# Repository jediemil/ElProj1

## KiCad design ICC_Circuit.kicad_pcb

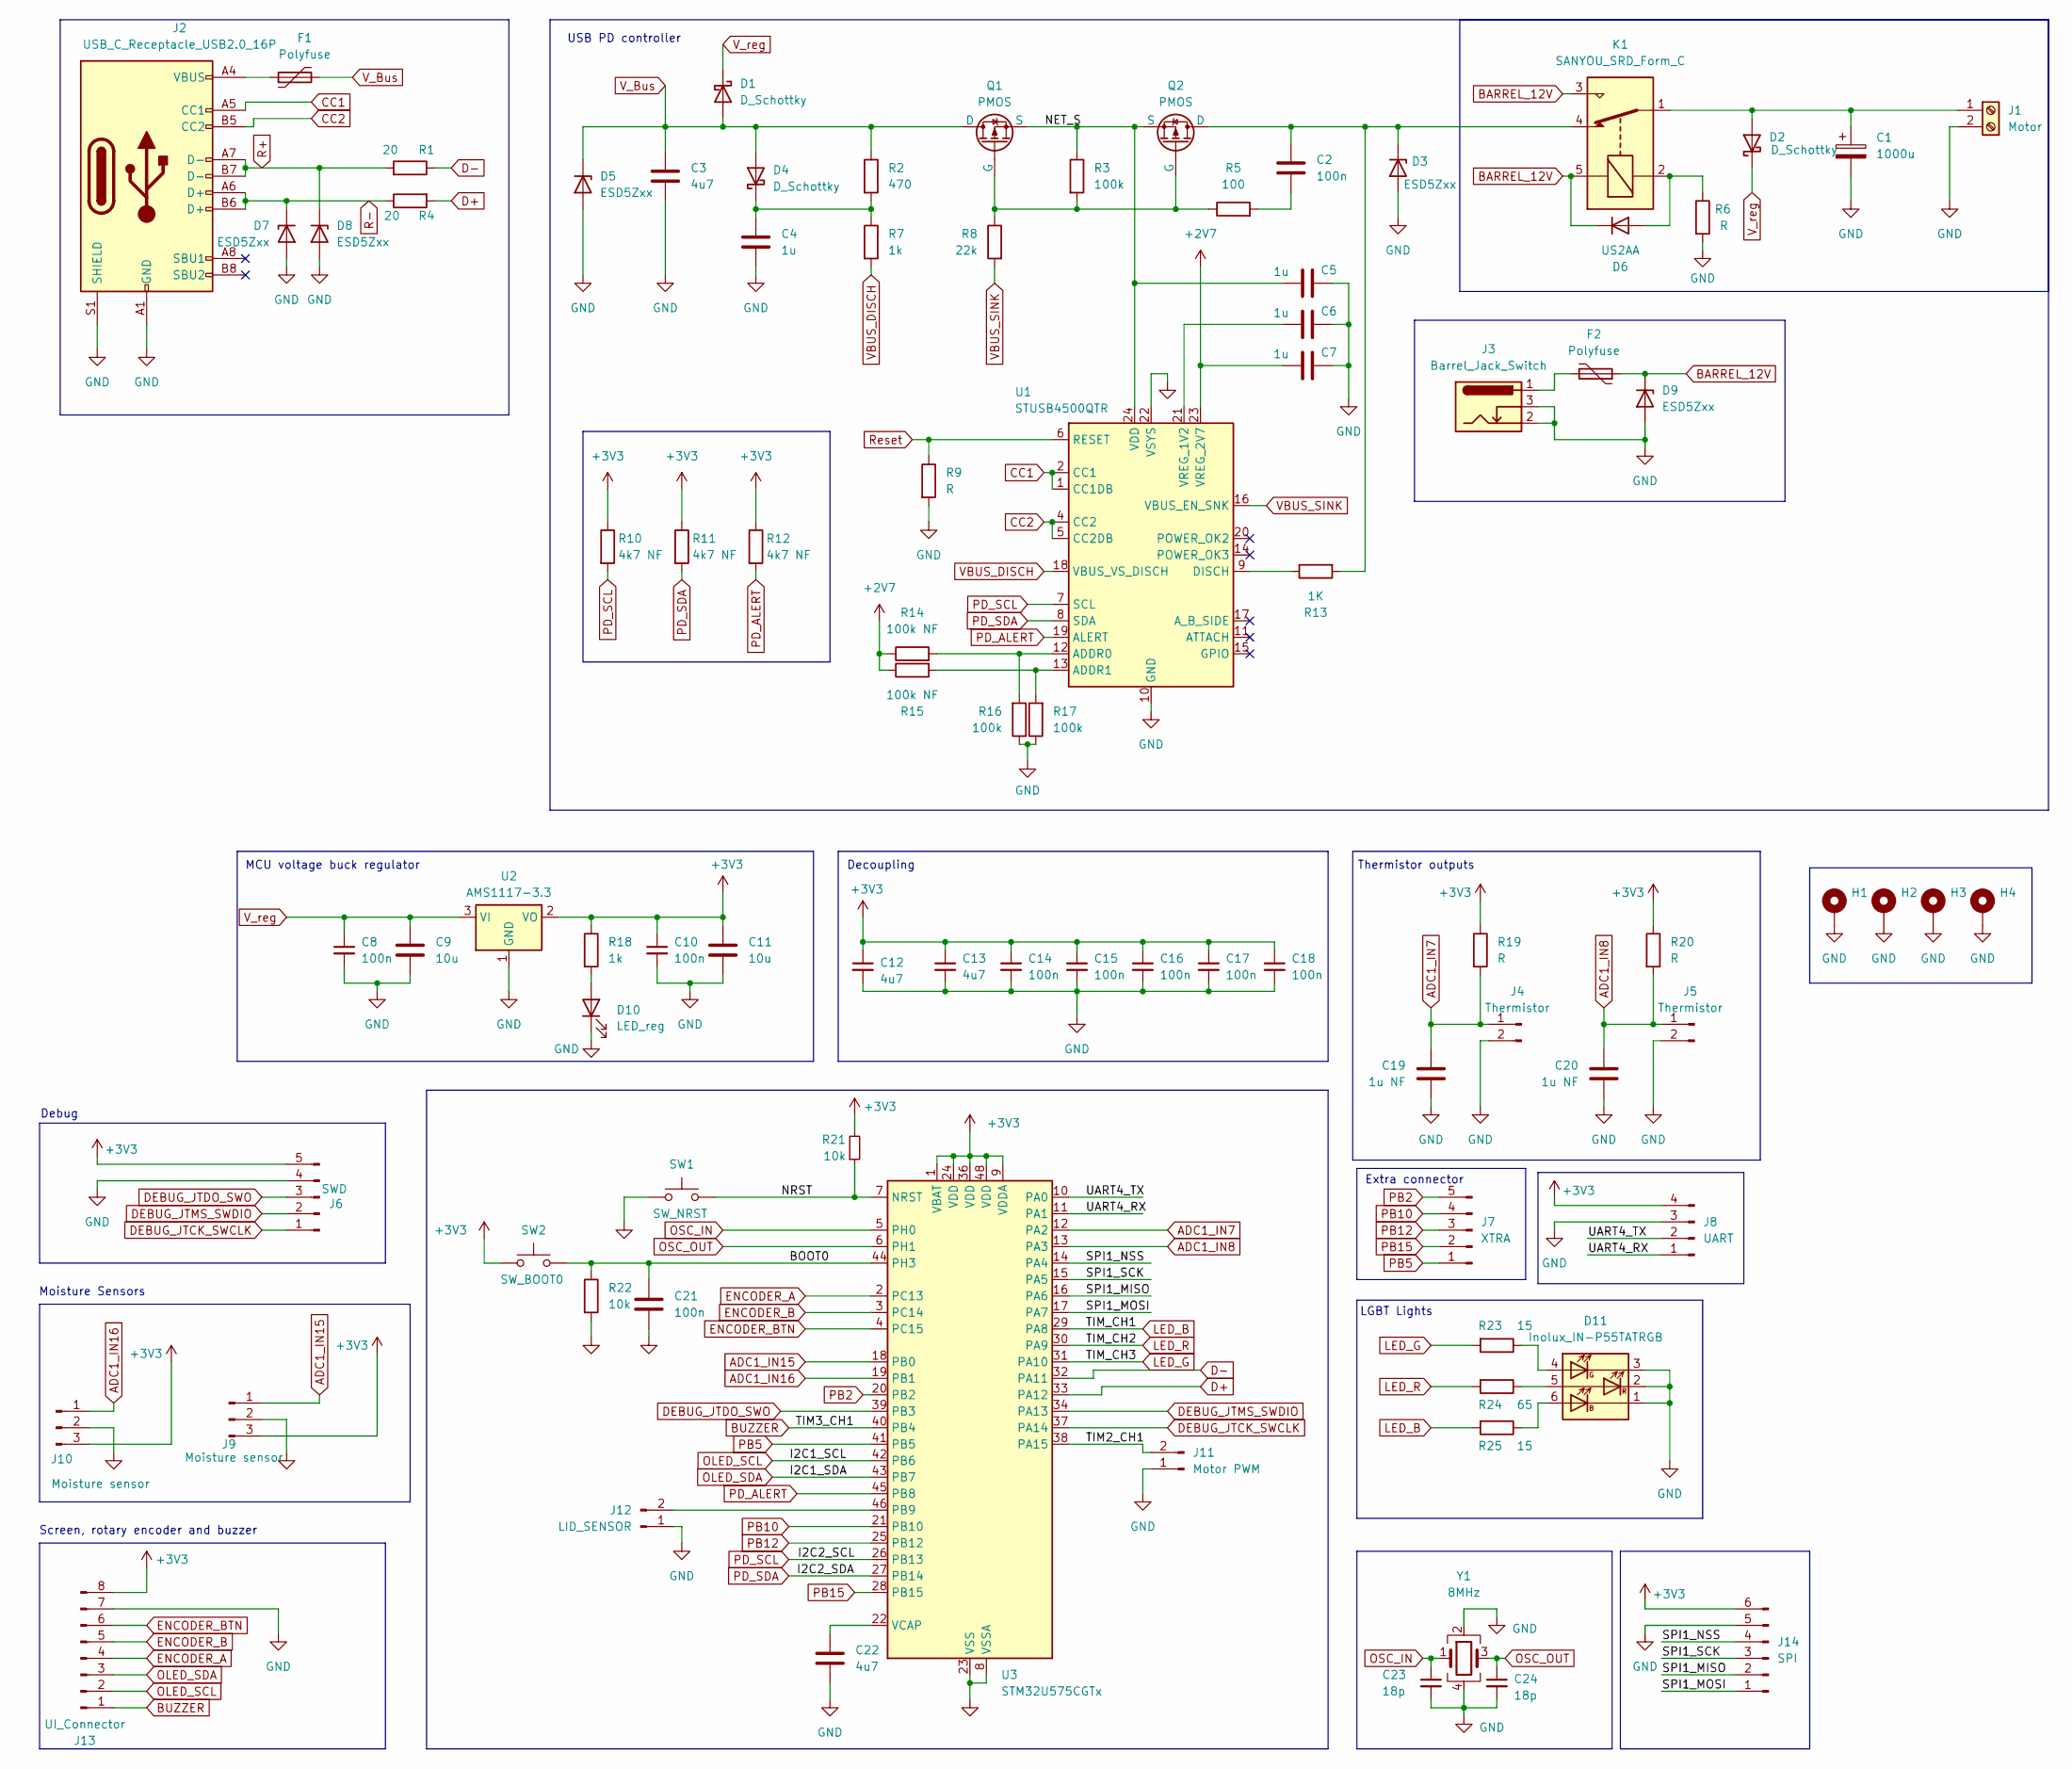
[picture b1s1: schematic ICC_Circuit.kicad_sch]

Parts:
C1: 1000u; CP_Radial_D10.0mm_P5.00mm
C2, C8, C10, C14, C15, C16, C17, C18, C21: 100n; C_0603_1608Metric
C3, C12, C13, C22: 4u7; C_0603_1608Metric
C4, C5, C6, C7: 1u; C_0603_1608Metric
C9, C11: 10u; C_0603_1608Metric
C19, C20: 1u NF; C_0603_1608Metric
C23, C24: 18p; C_0603_1608Metric
D1, D2, D4: D_Schottky; SOT-23_SpecialNC_Schottky
D3, D5, D7, D8, D9: ESD5Zxx; D_SMB
D6: US2AA; D_SMA
D10: LED_reg; LED_0603_1608Metric
D11: Inolux_IN-P55TATRGB; LED_Inolux_IN-P55TATRGB_PLCC6_5.0x5.5mm_P1.8mm
F1, F2: Polyfuse; 0ZRP0400FF custom Fuse
H1, H2, H3, H4: MountingHole_Pad; MountingHole_3.2mm_M3
J1: Motor; TerminalBlock_bornier-2_P5.08mm
J2: USB_C_Receptacle_USB2.0_16P; USB_C_Receptacle_GCT_USB4105-xx-A_16P_TopMnt_Horizontal
J3: Barrel_Jack_Switch; BarrelJack_GCT_DCJ200-10-A_Horizontal
J4, J5: Thermistor; JST_XH_S2B-XH-A-1_1x02_P2.50mm_Horizontal
J6: SWD; PinHeader_1x05_P2.54mm_Vertical
J7: XTRA; PinHeader_1x05_P2.54mm_Vertical
J8: UART; PinHeader_1x04_P2.54mm_Vertical
J9, J10: Moisture sensor; JST_XH_S3B-XH-A-1_1x03_P2.50mm_Horizontal
J11: Motor PWM; PinHeader_1x02_P2.54mm_Vertical
J12: LID_SENSOR; JST_XH_S2B-XH-A-1_1x02_P2.50mm_Horizontal
J13: UI_Connector; JST_XH_S8B-XH-A-1_1x08_P2.50mm_Horizontal
J14: SPI; PinHeader_1x06_P2.54mm_Vertical
K1: SANYOU_SRD_Form_C; Relay_SPDT_SANYOU_SRD_Series_Form_C
Q1, Q2: PMOS; Custom_PMOS_bajs_TSOP-6_1.65x3.05mm_P0.95mm
R1, R4: 20; R_0603_1608Metric
R2: 470; R_0603_1608Metric
R3, R16, R17: 100k; R_0603_1608Metric
R5: 100; R_0603_1608Metric
R6, R9, R19, R20: R; R_0603_1608Metric
R7, R18: 1k; R_0603_1608Metric
R8: 22k; R_0603_1608Metric
R10, R11, R12: 4k7 NF; R_0603_1608Metric
R13: 1K; R_0603_1608Metric
R14, R15: 100k NF; R_0603_1608Metric
R21, R22: 10k; R_0603_1608Metric
R23, R25: 15; R_0603_1608Metric
R24: 65; R_0603_1608Metric
SW1: SW_NRST; CharliesButton
SW2: SW_BOOT0; CharliesButton
U1: STUSB4500QTR; QFN-24-1EP_4x4mm_P0.5mm_EP2.7x2.7mm
U2: AMS1117-3.3; SOT-223-3_TabPin2
U3: STM32U575CGTx; LQFP-48_7x7mm_P0.5mm
Y1: 8MHz; Crystal_SMD_3225-4Pin_3.2x2.5mm_HandSoldering

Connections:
+2V7: C7.1, R14.1, R15.1, U1.23 (VREG_2V7)
+3V3: C10.1, C11.1, C12.1, C13.1, C14.1, C15.1, C16.1, C17.1, C18.1, J6.5, J8.4, J9.3, J10.3, J13.8, J14.6, R10.1, R11.1, R12.1, R18.1, R19.1, R20.1, R21.2, SW2.1, U2.2 (VO), U3.1 (VBAT), U3.9 (VDDA), U3.24 (VDD), U3.36 (VDD), U3.48 (VDD)
/BOOT0: C21.1, R22.1, SW2.2, U3.44 (PH3)
/NET_S: C5.1, Q1.3 (S), Q2.3 (S), R3.1, U1.24 (VDD)
/NRST: R21.1, SW1.2, U3.7 (NRST)
/SPI1_MISO: J14.2, U3.16 (PA6)
/SPI1_MOSI: J14.1, U3.17 (PA7)
/SPI1_NSS: J14.4, U3.14 (PA4)
/SPI1_SCK: J14.3, U3.15 (PA5)
/TIM2_CH1: J11.2, U3.38 (PA15)
/UART4_RX: J8.1, U3.11 (PA1)
/UART4_TX: J8.2, U3.10 (PA0)
ADC1_IN7: C19.1, J4.1, R19.2, U3.12 (PA2)
ADC1_IN8: C20.1, J5.1, R20.2, U3.13 (PA3)
ADC1_IN15: J9.1, U3.18 (PB0)
ADC1_IN16: J10.1, U3.19 (PB1)
BARREL_12V: D6.1 (K), D9.1 (K), F2.1, K1.3, K1.5
BUZZER: J13.1, U3.40 (PB4)
CC1: J2.A5 (CC1), U1.1 (CC1DB), U1.2 (CC1)
CC2: J2.B5 (CC2), U1.4 (CC2), U1.5 (CC2DB)
D+: R4.2, U3.33 (PA12)
D-: R1.1, U3.32 (PA11)
DEBUG_JTCK_SWCLK: J6.1, U3.37 (PA14)
DEBUG_JTDO_SWO: J6.3, U3.39 (PB3)
DEBUG_JTMS_SWDIO: J6.2, U3.34 (PA13)
ENCODER_A: J13.4, U3.2 (PC13)
ENCODER_B: J13.5, U3.3 (PC14)
ENCODER_BTN: J13.6, U3.4 (PC15)
GND: C1.2, C3.2, C4.2, C5.2, C6.2, C7.2, C8.2, C9.2, C10.2, C11.2, C12.2, C13.2, C14.2, C15.2, C16.2, C17.2, C18.2, C19.2, C20.2, C21.2, C22.2, C23.2, C24.2, D3.2 (A), D5.2 (A), D7.2 (A), D8.2 (A), D9.2 (A), D10.1 (K), D11.1 (KB), D11.2 (KR), D11.3 (KG), H1.1, H2.1, H3.1, H4.1, J1.2, J2.A1 (GND), J2.A12 (GND), J2.B1 (GND), J2.B12 (GND), J2.S1 (SHIELD), J3.2, J3.3, J4.2, J5.2, J6.4, J8.3, J9.2, J10.2, J11.1, J12.1, J13.7, J14.5, R6.2, R9.2, R16.1, R17.1, R22.2, SW1.1, U1.10 (GND), U1.22 (VSYS), U1.25 (GND), U2.1 (GND), U3.8 (VSSA), U3.23 (VSS), U3.35 (VSS), U3.47 (VSS), Y1.2, Y1.4
LED_B: R25.2, U3.29 (PA8)
LED_G: R23.2, U3.31 (PA10)
LED_R: R24.2, U3.30 (PA9)
unnamed: C2.2, R5.2
unnamed: C1.1, D2.2 (A), J1.1, K1.1
unnamed: C2.1, D3.1 (K), K1.4, Q2.1 (D), R13.2
unnamed: C4.1, D4.1 (K), R2.2, R7.1
unnamed: D6.2 (A), K1.2, R6.1
unnamed: D10.2 (A), R18.2
unnamed: D11.6 (AB), R25.1
unnamed: D11.4 (AG), R23.1
unnamed: D11.5 (AR), R24.1
unnamed: F1.1, J2.A4 (VBUS), J2.A9 (VBUS), J2.B4 (VBUS), J2.B9 (VBUS)
unnamed: F2.2, J3.1
unnamed: J12.2, U3.46 (PB9)
unnamed: Q1.2 (G), Q2.2 (G), R3.2, R5.1, R8.1
unnamed: R14.2, R16.2, U1.12 (ADDR0)
unnamed: R15.2, R17.2, U1.13 (ADDR1)
unnamed: R13.1, U1.9 (DISCH)
unnamed: C6.1, U1.21 (VREG_1V2)
unnamed: C22.1, U3.22 (VCAP)
OLED_SCL: J13.2, U3.42 (PB6)
OLED_SDA: J13.3, U3.43 (PB7)
OSC_IN: C23.1, U3.5 (PH0), Y1.1
OSC_OUT: C24.1, U3.6 (PH1), Y1.3
PB2: J7.5, U3.20 (PB2)
PB5: J7.1, U3.41 (PB5)
PB10: J7.4, U3.21 (PB10)
PB12: J7.3, U3.25 (PB12)
PB15: J7.2, U3.28 (PB15)
PD_ALERT: R12.2, U1.19 (ALERT), U3.45 (PB8)
PD_SCL: R10.2, U1.7 (SCL), U3.26 (PB13)
PD_SDA: R11.2, U1.8 (SDA), U3.27 (PB14)
R+: D8.1 (K), J2.A7 (D-), J2.B7 (D-), R1.2
R-: D7.1 (K), J2.A6 (D+), J2.B6 (D+), R4.1
Reset: R9.1, U1.6 (RESET)
VBUS_DISCH: R7.2, U1.18 (VBUS_VS_DISCH)
VBUS_SINK: R8.2, U1.16 (VBUS_EN_SNK)
V_Bus: C3.1, D1.2 (A), D4.2 (A), D5.1 (K), F1.2, Q1.1 (D), R2.1
V_reg: C8.1, C9.1, D1.1 (K), D2.1 (K), U2.3 (VI)

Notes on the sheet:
Thermistor outputs
Debug
MCU voltage buck regulator
Extra connector
LGBT Lights
Moisture Sensors
Screen, rotary encoder and buzzer
USB PD controller
Decoupling

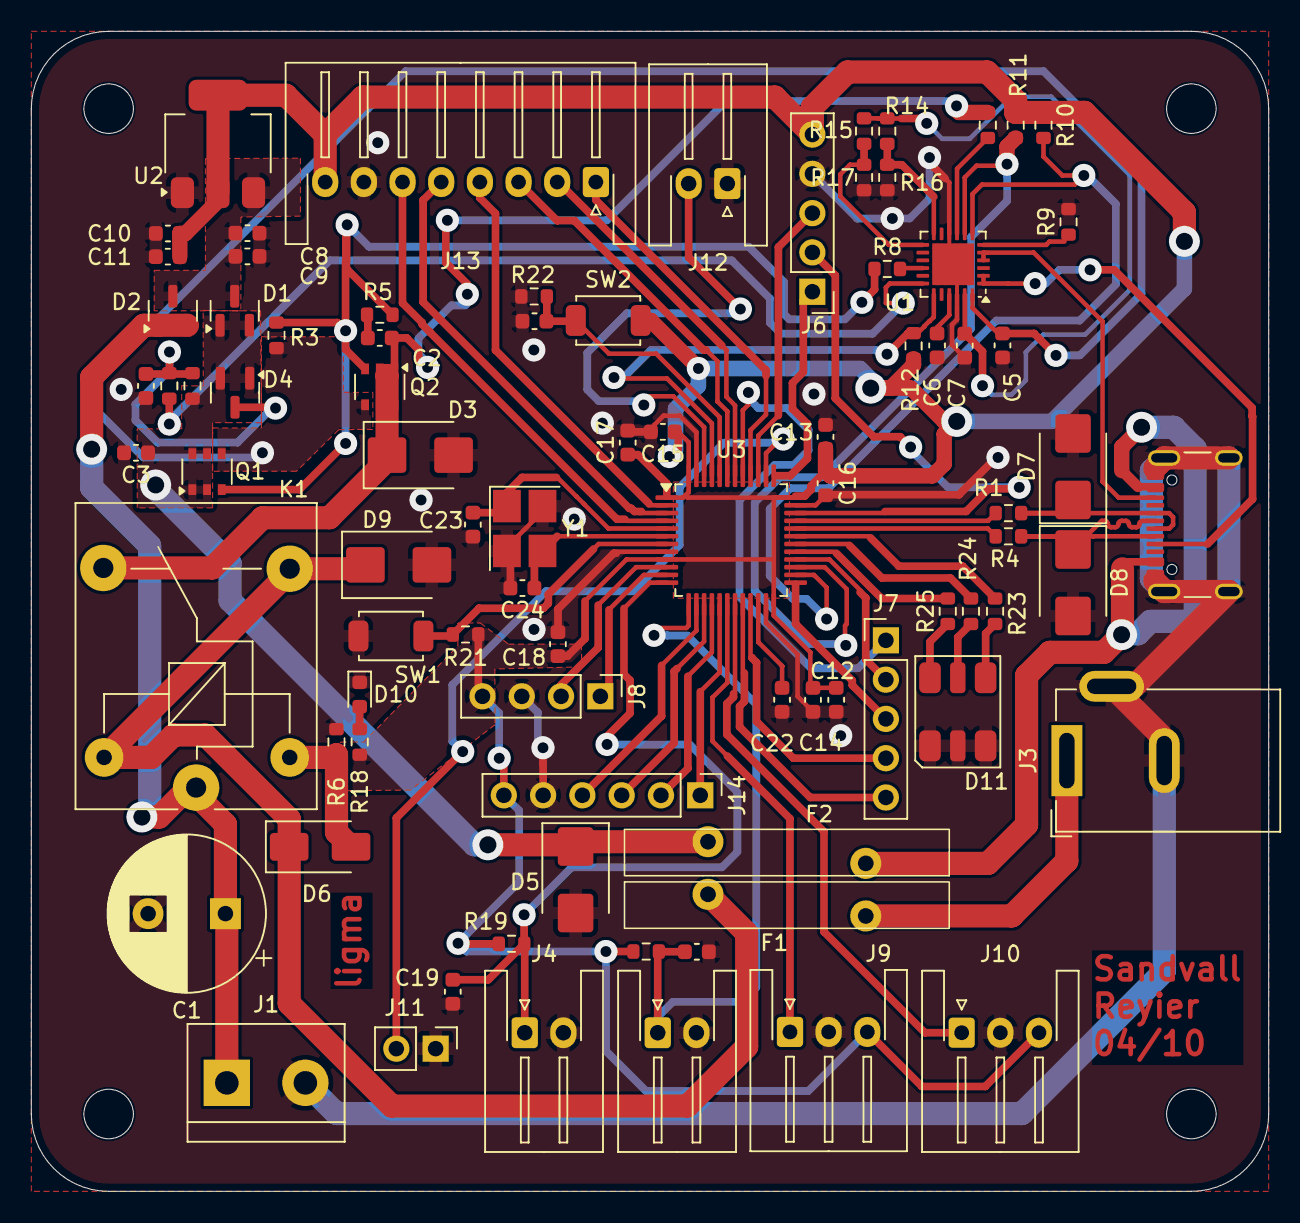
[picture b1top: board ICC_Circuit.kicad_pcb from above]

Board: 2 copper layers, 80.0 x 75.0 mm, 89 parts (0 on the bottom side), 69 nets.

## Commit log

2025-04-03 'aaa'
2025-04-03 aaa2
2025-04-03 Assigned footprints
2025-04-04 Started layout, moved ESD protection to the USB
2025-04-04 Updated PCB
2025-04-05 Relay and USB part of PCB done.
2025-04-06 95 percent completed PCB
2025-04-07 funkar?
2025-04-17 'aa'
